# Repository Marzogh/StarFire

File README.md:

# StarFire
Charlieplexed LED earrings with ATTiny85

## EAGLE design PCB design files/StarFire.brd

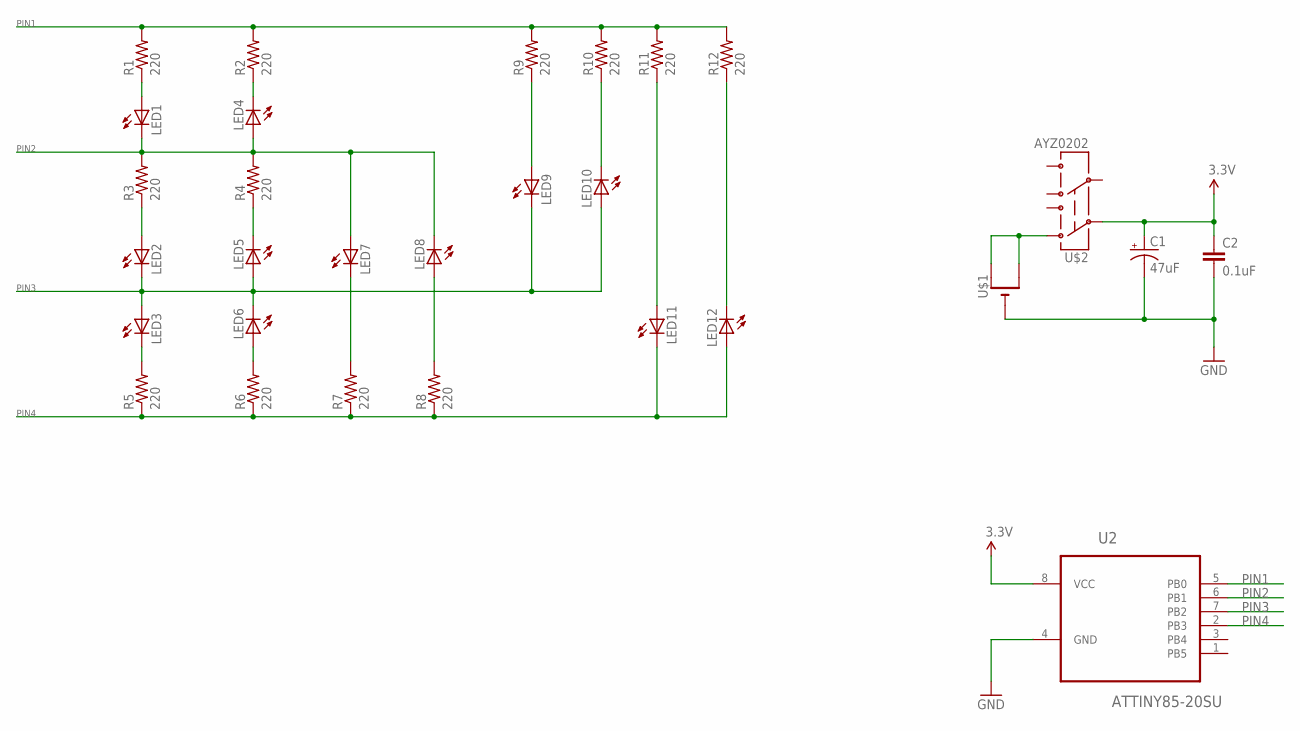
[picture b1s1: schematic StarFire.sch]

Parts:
C1: 47uF; EIA3528
C2: 0.1uF; 0603-CAP
LED1, LED2, LED3, LED4, LED5, LED6, LED7, LED8, LED9, LED10, LED11, LED12: LEDCHIP-LED0603; CHIP-LED0603
R1, R2, R3, R4, R5, R6, R7, R8, R9, R10, R11, R12: 220; 0402-RES
U2: ATTINY85-20SU; SOIC127P798X216-8N
U$1: CR1220SMT; CR1220-SMD
U$2: AYZ0202

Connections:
3.3V: C1.A (+), C2.1, U2.8 (VCC), U$2.2
GND: C1.C (-), C2.2, U2.4 (GND), U$1.-
unnamed: LED1.A, R1.1
unnamed: LED4.C, R2.1
unnamed: LED2.A, R3.1
unnamed: LED5.C, R4.1
unnamed: LED3.C, R5.2
unnamed: LED6.A, R6.2
unnamed: LED7.C, R7.2
unnamed: LED8.A, R8.2
unnamed: LED9.A, R9.1
unnamed: LED10.C, R10.1
unnamed: LED11.A, R11.1
unnamed: LED12.C, R12.1
unnamed: U$1.+$1 (+), U$2.3 (1)
PIN1: R1.2, R2.2, R9.2, R10.2, R11.2, R12.2, U2.5 (PB0)
PIN2: LED1.C, LED4.A, LED7.A, LED8.C, R3.2, R4.2, U2.6 (PB1)
PIN3: LED2.C, LED3.A, LED5.A, LED6.C, LED9.C, LED10.A, U2.7 (PB2)
PIN4: LED11.C, LED12.A, R5.1, R6.1, R7.1, R8.1, U2.2 (PB3)

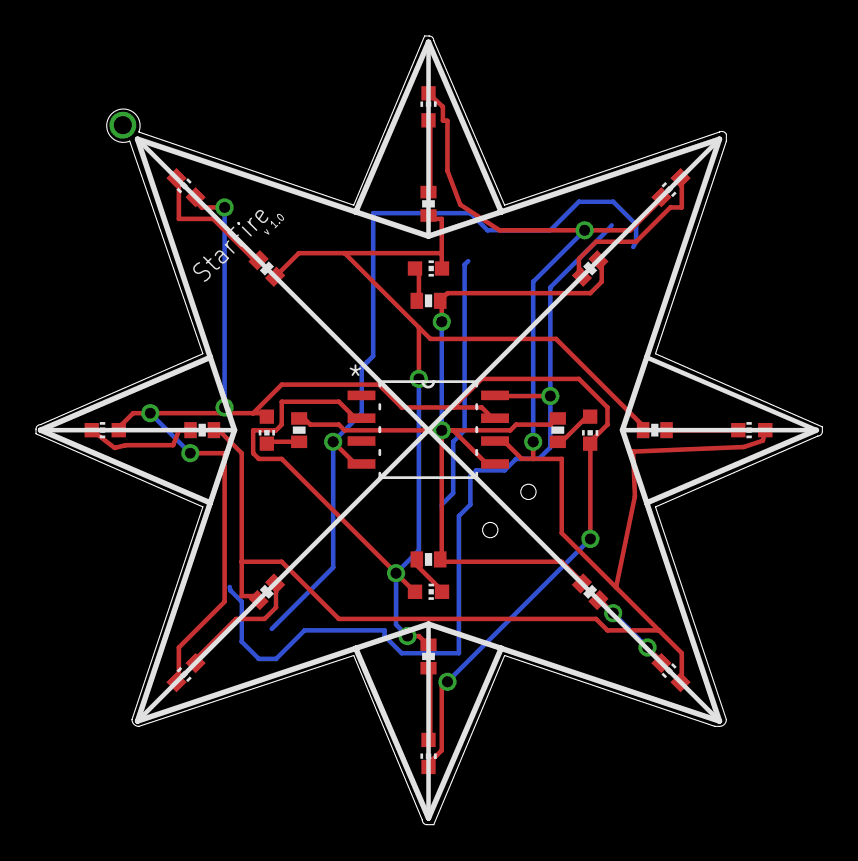
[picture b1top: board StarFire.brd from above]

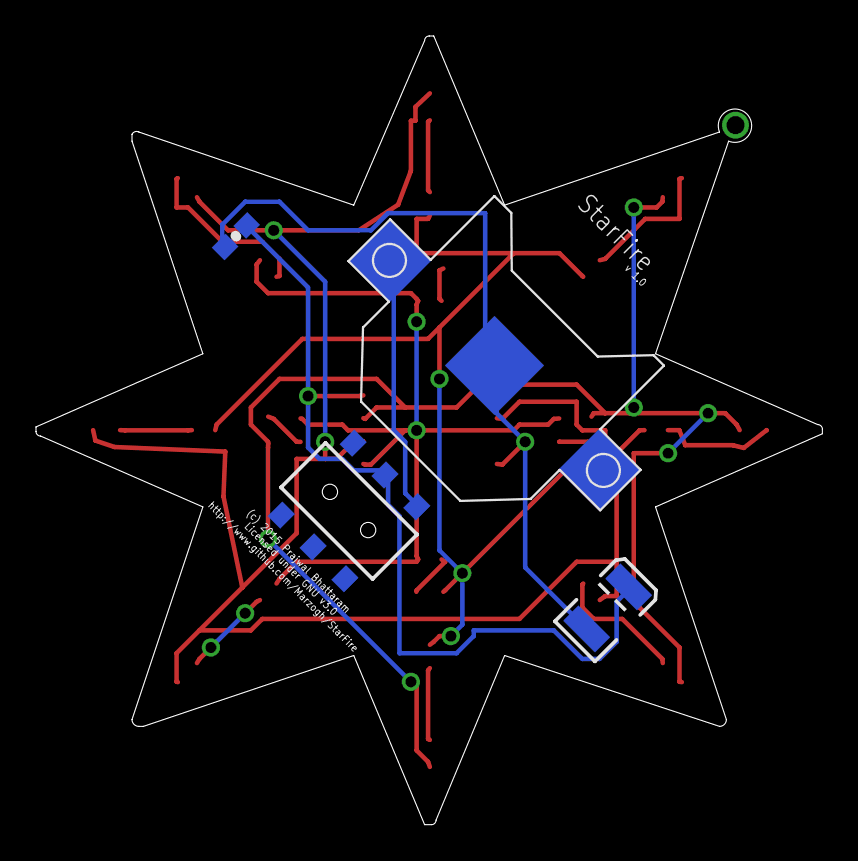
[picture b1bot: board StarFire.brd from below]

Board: 2 copper layers, 43.7 x 43.8 mm, 29 parts (4 on the bottom side), 19 nets.

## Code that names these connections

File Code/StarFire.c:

/*
|~~~~~~~~~~~~~~~~~~~~~~~~~~~~~~~~~~~~~~~~~~~~~~~~~~~~~~~~~~~~~~~~~~~~~~~~~~~~~~~~~~~~~~~~~~~~~~~~~~~~~~~~~~~~~~~~~~~~~~~~~~~~~~~~~~~~~~~~~~~~~~~|
|                                                            StarFire LED Earrings                                                              |
|                                                                  StarFire.c                                                                   |
|                                                                 Version 1.0                                                                   |
|                                                              Prajwal Bhattaram                                                                |
|                                                                  16.03.2016                                                                   |
|~~~~~~~~~~~~~~~~~~~~~~~~~~~~~~~~~~~~~~~~~~~~~~~~~~~~~~~~~~~~~~~~~~~~~~~~~~~~~~~~~~~~~~~~~~~~~~~~~~~~~~~~~~~~~~~~~~~~~~~~~~~~~~~~~~~~~~~~~~~~~~~|
*/

#include <avr/io.h>
#include <util/delay.h>
#include <avr/interrupt.h>

void setLED(uint8_t LED);
/*
    Truth table for LED matrix
    LEDs connected to PB0 (PIN1), PB1 (PIN2), PB2 (PIN3) and PB3 (PIN4)

    Led    | Pin High | Pin Low | Pin Disc. | PORTB | DDRB |
    --------------------------------------------------------
    1      | 1        | 2       | 3, 4      | 0x01  | xF3  |
    2      | 2        | 3       | 1, 4      | 0x02  | xF6  |
    3      | 3        | 4       | 1, 2      | 0x04  | xFC  |
    4      | 2        | 1       | 3, 4      | 0x02  | xF3  |
    5      | 3        | 2       | 1, 4      | 0x04  | xF6  |
    6      | 4        | 3       | 1, 2      | 0x08  | xFC  |
    7      | 2        | 4       | 1, 3      | 0x02  | xFA  |
    8      | 4        | 2       | 1, 3      | 0x08  | xFA  |
    9      | 1        | 3       | 2, 4      | 0x01  | xF5  |
    10     | 3        | 1       | 2, 4      | 0x04  | xF5  |
    11     | 1        | 4       | 2, 3      | 0x01  | xF9  |
    12     | 4        | 1       | 2, 3      | 0x08  | xF9  |

7654 3210
---------
1111 0000
0000 1111

*/
uint8_t currentLED;
uint8_t _DDR[12] {0xF3, 0XF6, 0XFC, 0XF3, 0XF6, 0XFC, 0XFA, 0XFA, 0XF5, 0XF5, 0XF9, 0XF9};
uint8_t _PORT[12] {0X01, 0X02, 0X04, 0X02, 0X04, 0X08, 0X02, 0X08, 0X01, 0X04, 0X01, 0X08}

void main()
{
  PORTB &= 0xF0;            // Set bits 0 to 3 to 0, i.e. off
  DDRB |= 0x0F;             // Set lower 4 bits to 1, i.e. output

  // Set up timer prescalar to FCpu/256 @ 1MHz
  TCCR0B |= (_BV(CS02));

  // Set timer to CTC mode
  TCCR0A |= _BV(WGM01);
  // Enable CTC interrupt
  TIMSK |= _BV(OCIE0A);
  // Enable global interrupts
  sei();

  // Set timer to compare 1/10 second
  OCR0A = 77;

  while(1)
  {
    //Turn on an LED
    setLED(currentLED);
  }
}

// Handle timer interrupt
// this triggers the interrupt every 1/4th of a second
ISR(TIMER0_COMPA_vect)
{
  //int i;

    /*if (i != currentLED)
    {
      currentLED = i;
    }
    else
    {
      i = rand() % 7;
    }*/
  currentLED = rand() % 49;
}

void setLED(uint8_t LED)
{
  // Clear existing status, we can only drive one LED at a time
  PORTB &= 0xF0;    // Set the lower 3 bits to 0, i.e. off
  DDRB |= 0x0F;   // Set the lower 3 bits to 1, i.e. output

  // Now set the LED as determined by the interrupt code
  DDRB &= _DDR[LED];   // Disconnect the pin as set in the DDR array
  PORTB |= _PORT[LED]
}

// Switch the state of the LED from on to off or from off to on
/*void setLED(uint8_t LED)
{
  //Clear existing status, we can only drive one LED at a time
  PORTB &= 0xF0;    // Set the lower 3 bits to 0, i.e. off
  DDRB |= 0x0F;   // Set the lower 3 bits to 1, i.e. output

  switch (LED)
  {
    case 0: 
      DDRB  &= 0xEF;  // Disconnect the nr. 2 pin
      PORTB |= 0x04;  // Set pin 0 to high and pin 1 to low
      break;
    
    case 1: 
      DDRB  &= 0xEF;  // Disconnect the nr. 2 pin
      PORTB |= 0x08;  // Set pin 1 to high and pin 0 to low
      break;
    
    case 2: 
      DDRB  &= 0xFB;  // Disconnect the nr. 0 pin
      PORTB |= 0x08;  // Set pin 1 to high and pin 2 to low
      break;        

    case 3: 
      DDRB  &= 0xFB;  // Disconnect the nr. 0 pin
      PORTB |= 0x10;  // Set pin 2 to high and pin 1 to low
      break;              
            
    case 4: 
      DDRB  &= 0xF7;  // Disconnect the nr. 1 pin
      PORTB |= 0x04;  // Set pin 0 to high and pin 2 to low
      break;
    
    case 5: 
      DDRB  &= 0xF7;  // Disconnect the nr. 1 pin
      PORTB |= 0x10;  // Set pin 2 to high and pin 0 to low
      break;

    default: 
      break;
  }
}*/

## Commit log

2016-03-15 Added v1.0 of board
2016-03-16 cleanup and sort
2016-03-16 Added test code
2016-03-16 Fixed routing errors
2016-03-22 Added gitignore

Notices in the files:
PCB design files/StarFire.brd:
(c) 2015 Prajwal Bhattaram
Licensed under GNU v3.0
parts and their libraries:
SparkFun-Capacitors: Licensing: Creative Commons ShareAlike 4.0 International - https://creativecommons.org/licenses/by-sa/4.0
